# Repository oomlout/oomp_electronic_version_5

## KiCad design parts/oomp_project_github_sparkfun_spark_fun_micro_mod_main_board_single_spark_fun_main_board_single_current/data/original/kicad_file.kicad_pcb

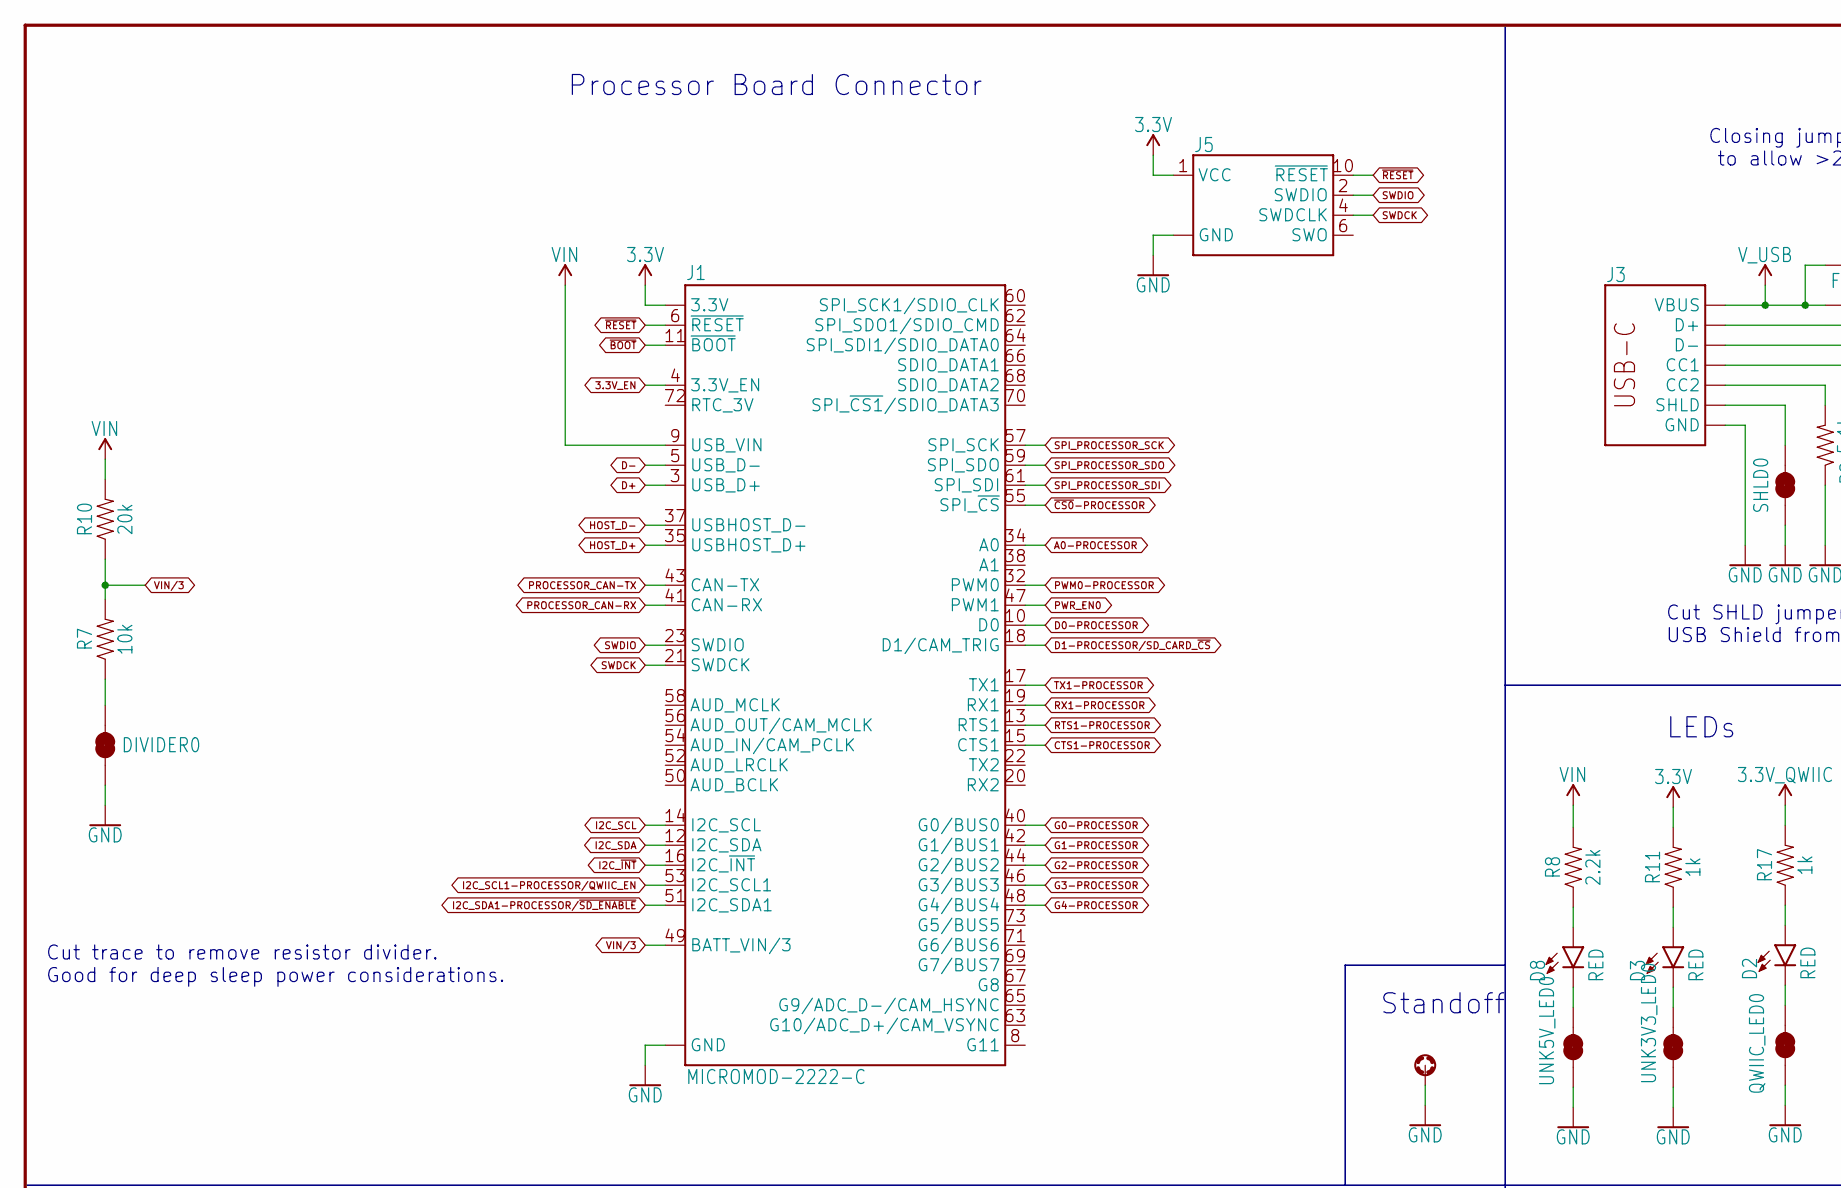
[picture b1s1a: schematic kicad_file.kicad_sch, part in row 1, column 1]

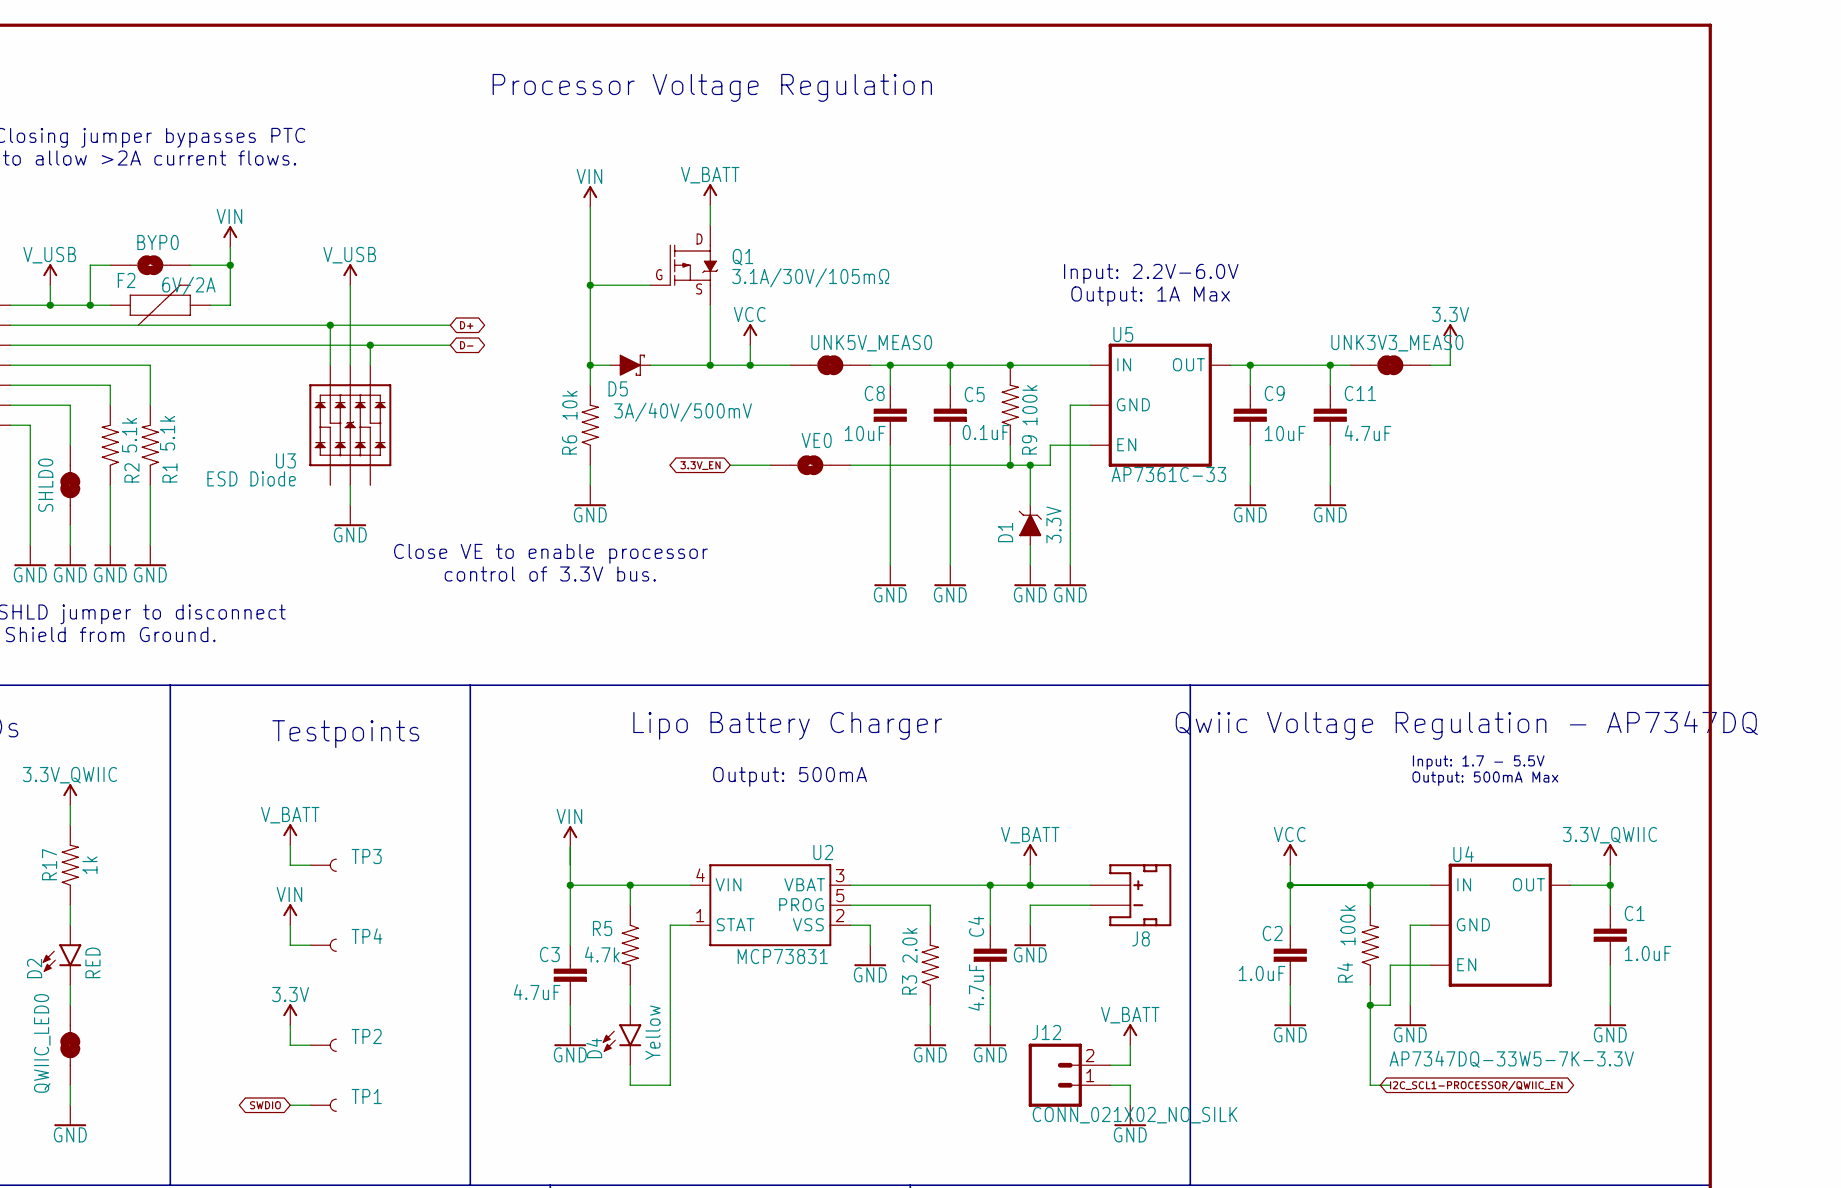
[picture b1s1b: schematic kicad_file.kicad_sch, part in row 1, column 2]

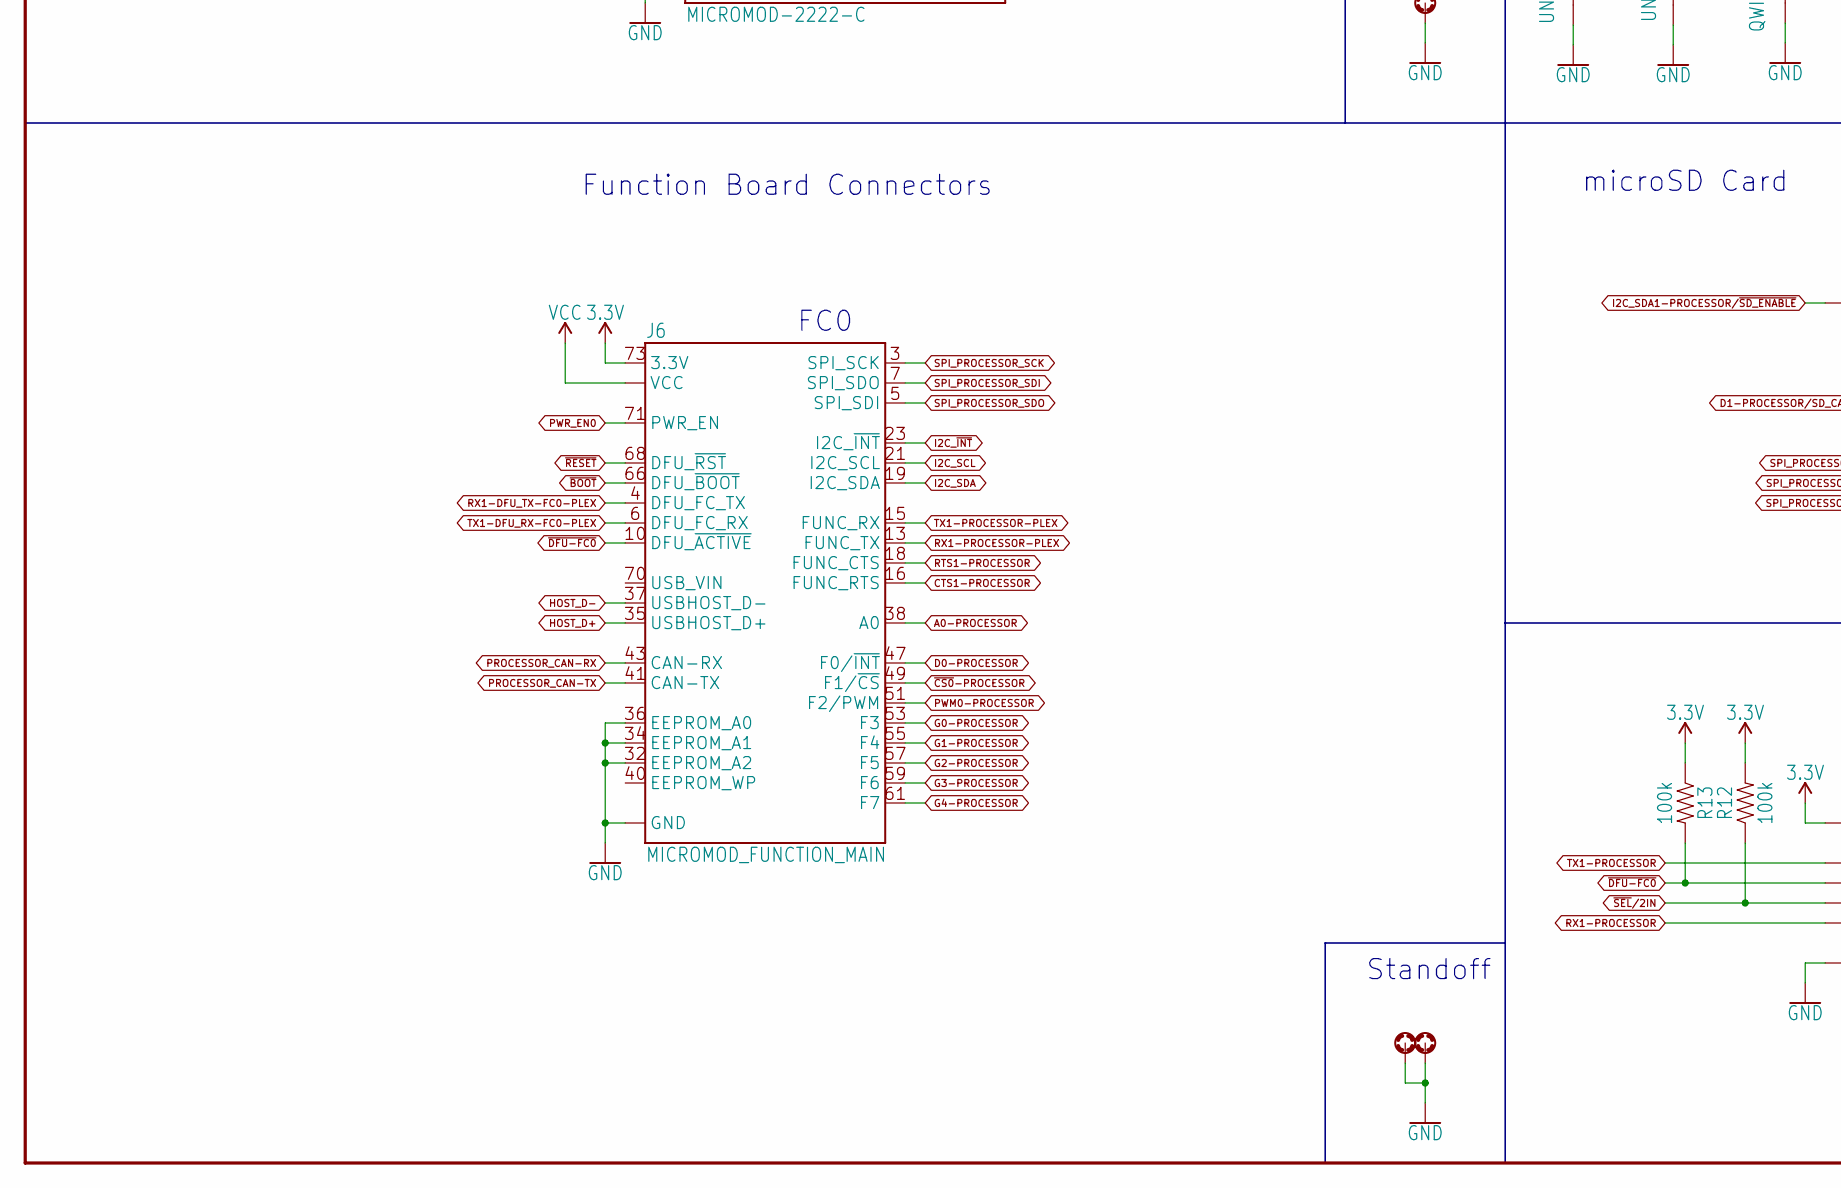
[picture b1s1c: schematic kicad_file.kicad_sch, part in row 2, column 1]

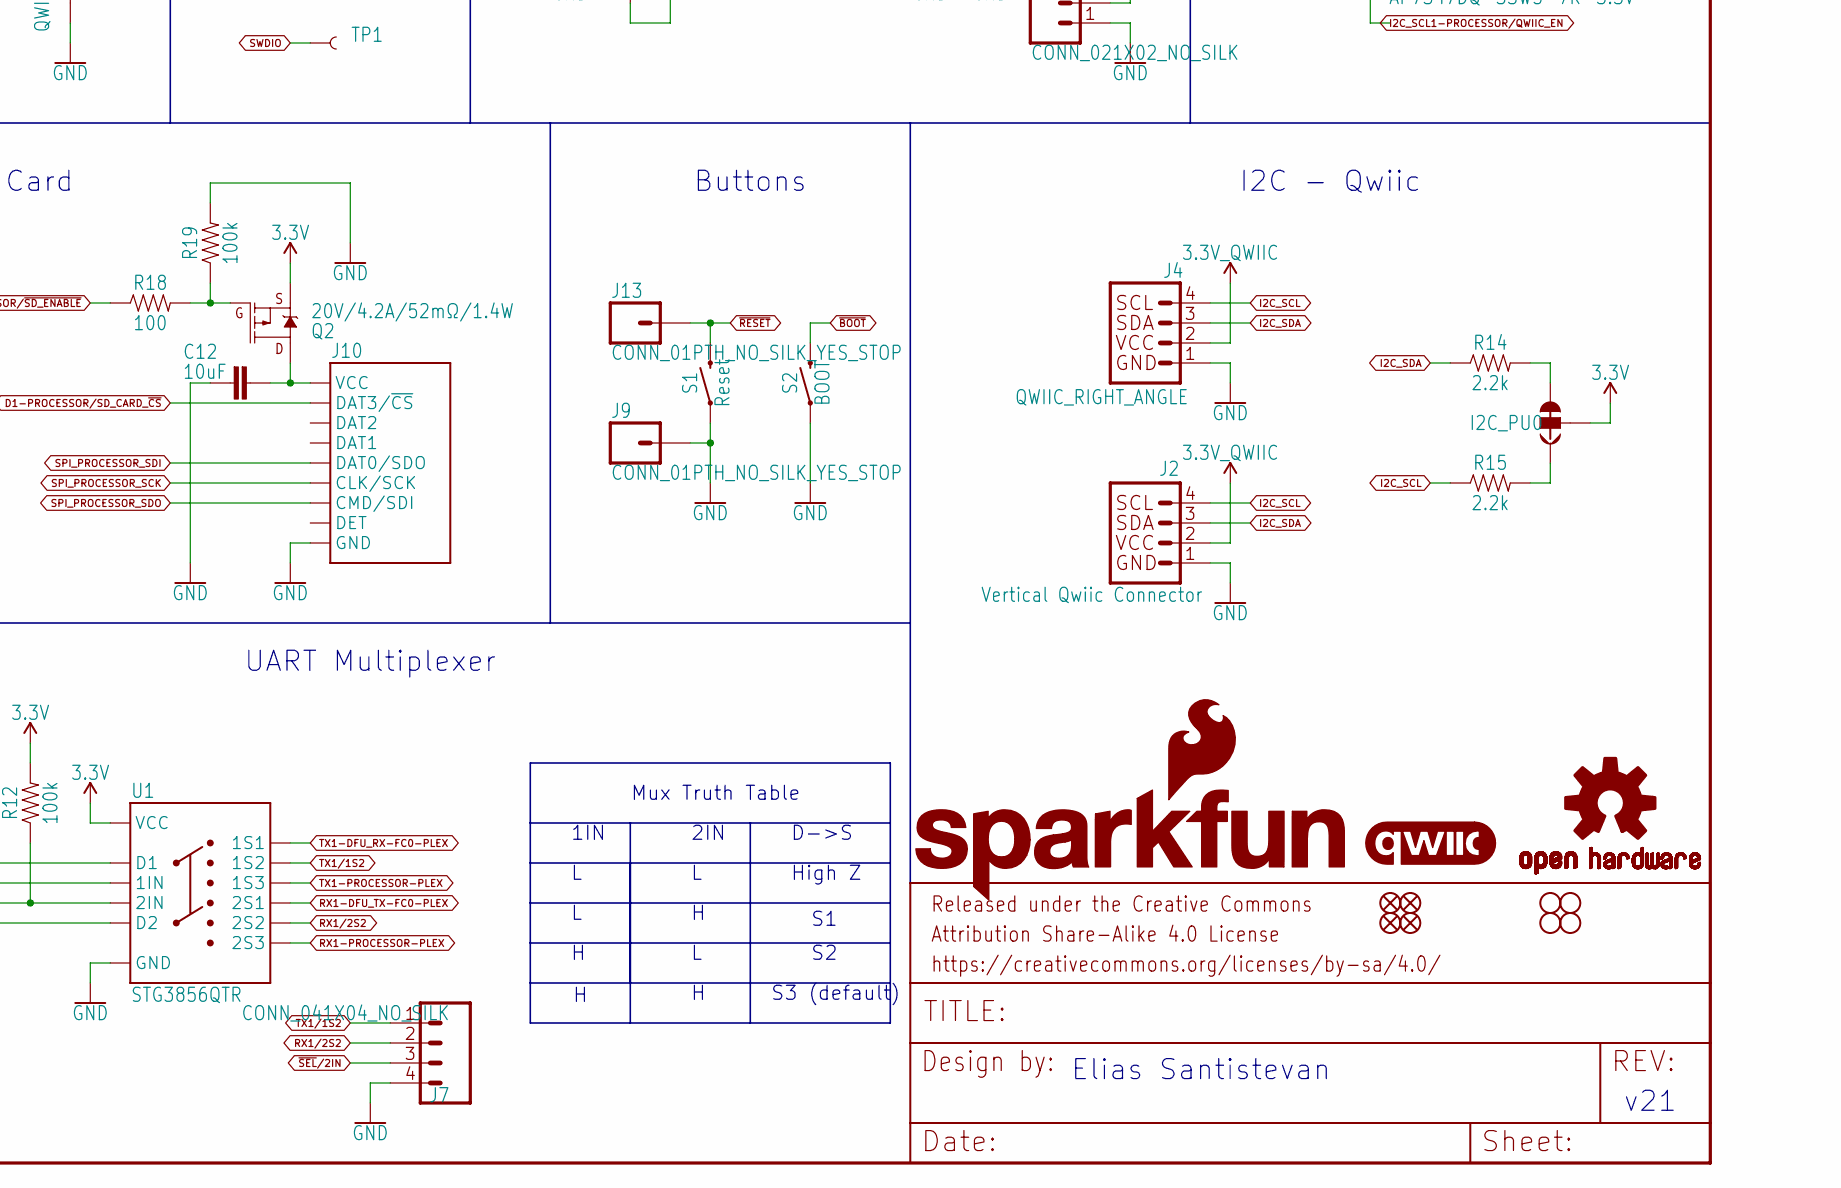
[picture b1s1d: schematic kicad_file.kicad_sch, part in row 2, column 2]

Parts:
BYP0: JUMPER-SMT_2_NO_SILK; SMT-JUMPER_2_NO_SILK
C1, C2: 1.0uF; 0603
C3, C4, C11: 4.7uF; 0603
C5: 0.1uF; 0603
C8: 10uF; 0805
C9, C12: 10uF; 0603
D1: 3.3V; SOD-323
D2, D3, D8: RED; LED-0603
D4: Yellow; LED-0603
D5: 3A/40V/500mV; SMA-DIODE
DIVIDER0: JUMPER-SMT_2_NC_TRACE_SILK; SMT-JUMPER_2_NC_TRACE_SILK
F2: 6V/2A; 1210
FD1, FD2, FD3, FD4: FIDUCIAL1X2; FIDUCIAL-1X2
FRAME1: FRAME-LEDGER; CREATIVE_COMMONS
H2, H4, H8: STAND-OFF-REFLOW-M2.5_2.5MM_TALL; STAND-OFF-REFLOW-M2.5
H14, H15, H16, H17: STAND-OFFTIGHT; STAND-OFF-TIGHT
I2C_PU0: JUMPER-SMT_3_2-NC_TRACE_SILK; SMT-JUMPER_3_2-NC_TRACE_SILK
J1: MICROMOD-2222-C; M.2-CONNECTOR-E
J2: Vertical Qwiic Connector; JST04_1MM_VERT
J3: USB_C_2-LAYER_PADS; USB-C-16P-2LAYER-PADS
J4: QWIIC_RIGHT_ANGLE; JST04_1MM_RA
J5: CORTEX_JTAG_DEBUG_MINIMUM_PTH; 2X5-PTH-1.27MM
J6: MICROMOD_FUNCTION_MAIN; M.2-CONNECTOR-E-FUNCTION-STANDARD
J7: CONN_041X04_NO_SILK; 1X04_NO_SILK
J8: JST_2MM_MALE; JST-2-SMD
J9, J13: CONN_01PTH_NO_SILK_YES_STOP; 1X01_NO_SILK
J10: MICRO-SD-PUSH-PUSH-EXT-PIN; MICROSD-EXTERNALPIN
J12: CONN_021X02_NO_SILK; 1X02_NO_SILK
LOGO1: QWIIC_LOGO_8MM; QWIIC_8MM
LOGO2: SFE_LOGO_NAME_FLAME.3_INCH; SFE_LOGO_NAME_FLAME_.3
LOGO3: OSHW-LOGOL; OSHW-LOGO-L
Q1: 3.1A/30V/105mΩ; SOT23-3
Q2: 20V/4.2A/52mΩ/1.4W; SOT23-3
QWIIC_LED0: JUMPER-SMT_2_NC_TRACE_SILK; SMT-JUMPER_2_NC_TRACE_SILK
R1, R2: 5.1k; 0603
R3: 2.0k; 0603
R4, R9, R12, R13, R19: 100k; 0603
R5: 4.7k; 0603
R6, R7: 10k; 0603
R8, R14, R15: 2.2k; 0603
R10: 20k; 0603
R11, R17: 1k; 0603
R18: 100; 0603
S1: Reset; TACTILE_SWITCH_SMD_5.2MM
S2: BOOT; TACTILE_SWITCH_SMD_5.2MM
SHLD0: JUMPER-SMT_2_NC_TRACE_SILK; SMT-JUMPER_2_NC_TRACE_SILK
TP1, TP2, TP3, TP4: TEST-POINT3X5; PAD.03X.05
U1: STG3856QTR; STG3856
U2: MCP73831; SOT23-5
U3: ESD Diode; SOT-23-6
U4: AP7347DQ-33W5-7K-3.3V; SOT25
U5: AP7361C-33; UDFN-8
UNK3V3_LED0, UNK5V_LED0: JUMPER-SMT_2_NC_TRACE_SILK; SMT-JUMPER_2_NC_TRACE_SILK
UNK3V3_MEAS0, UNK5V_MEAS0: JUMPER-COMBO_2_NC_TRACE; COMBO-JUMPER_2_NC_TRACE
VE0: JUMPER-SMT_2_NO_SILK; SMT-JUMPER_2_NO_SILK

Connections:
3.3V: I2C_PU0.2, J1.2 (3.3V), J1.74 (3.3V), J5.1 (VCC), J6.73 (3.3V), Q2.2 (S), R11.2, R12.2, R13.1, TP2.1, U1.P11 (VCC), UNK3V3_MEAS0.2, UNK3V3_MEAS0.4 (2)
3.3V_EN: J1.4 (3.3V_EN), VE0.1
3.3V_EN_VE: D1.C, R9.1, U5.5 (EN), VE0.2
3.3V_QWIIC: C1.1, J2.2, J4.2, R17.2, U4.5 (OUT)
3V3_MEAS: C9.1, C11.1, U5.1 (OUT), UNK3V3_MEAS0.1, UNK3V3_MEAS0.3 (1)
A0-PROCESSOR: J1.34 (A0), J6.38 (A0)
CTS1-PROCESSOR: J1.15 (CTS1), J6.16 (FUNC_RTS)
D0-PROCESSOR: J1.10 (D0), J6.47 (F0/~INT)
D1-PROCESSOR/SD_CARD_~CS: J1.18 (D1/CAM_TRIG), J10.2 (DAT3/~CS)
D+: J1.3 (USB_D+), J3.A6 (D+), J3.B6 (D+), U3.6 (IO4)
D-: J1.5 (USB_D-), J3.A7 (D-), J3.B7 (D-), U3.4 (IO3)
G0-PROCESSOR: J1.40 (G0/BUS0), J6.53 (F3)
G1-PROCESSOR: J1.42 (G1/BUS1), J6.55 (F4)
G2-PROCESSOR: J1.44 (G2/BUS2), J6.57 (F5)
G3-PROCESSOR: J1.46 (G3/BUS3), J6.59 (F6)
G4-PROCESSOR: J1.48 (G4/BUS4), J6.61 (F7)
GND: C1.2, C2.2, C3.2, C4.2, C5.2, C8.2, C9.2, C11.2, C12.2, D1.A, DIVIDER0.1, H2.1, H4.1, H8.1, J1.1 (GND), J1.7 (GND), J1.33 (GND), J1.36 (GND), J1.39 (GND), J1.45 (GND), J1.75 (GND), J2.1, J3.GND, J3.GND2 (GND), J4.1, J5.3 (GND), J5.5 (GND), J5.9 (GND), J6.1 (GND), J6.2 (GND), J6.8 (GND), J6.32 (EEPROM_A2), J6.33 (GND), J6.34 (EEPROM_A1), J6.36 (EEPROM_A0), J6.39 (GND), J6.45 (GND), J6.75 (GND), J7.4, J8.1 (-), J9.1, J10.6 (GND), J10.10 (GND), J10.11 (GND), J10.12 (GND), J10.13 (GND), J12.1, QWIIC_LED0.1, R1.1, R2.1, R3.1, R6.1, R19.2, S1.1, S1.2 (1), S2.1, S2.2 (1), SHLD0.1, U1.P5 (GND), U2.2 (VSS), U3.2 (VSS), U4.2 (GND), U5.4 (GND), U5.EP (GND), UNK3V3_LED0.1, UNK5V_LED0.1
HOST_D+: J1.35 (USBHOST_D+), J6.35 (USBHOST_D+)
HOST_D-: J1.37 (USBHOST_D-), J6.37 (USBHOST_D-)
I2C_SCL: J1.14 (I2C_SCL), J2.4, J4.4, J6.21 (I2C_SCL), R15.1
I2C_SCL1-PROCESSOR/QWIIC_EN: J1.53 (I2C_SCL1), R4.1, U4.3 (EN)
I2C_SDA: J1.12 (I2C_SDA), J2.3, J4.3, J6.19 (I2C_SDA), R14.1
I2C_SDA1-PROCESSOR/~SD_ENABLE: J1.51 (I2C_SDA1), R18.1
I2C_~INT: J1.16 (I2C_~INT), J6.23 (I2C_~INT)
unnamed: D8.C, UNK5V_LED0.2
unnamed: D3.A, R11.1
unnamed: J3.B5 (CC2), R2.2
unnamed: J3.A5 (CC1), R1.2
unnamed: R3.2, U2.5 (PROG)
unnamed: DIVIDER0.2, R7.1
unnamed: D4.C, U2.1 (STAT)
unnamed: D4.A, R5.2
unnamed: D3.C, UNK3V3_LED0.2
unnamed: I2C_PU0.3, R14.2
unnamed: D8.A, R8.1
unnamed: I2C_PU0.1, R15.2
unnamed: D2.A, R17.1
unnamed: D2.C, QWIIC_LED0.2
unnamed: C12.1, J10.4 (VCC), Q2.3 (D)
unnamed: Q2.1 (G), R18.2, R19.1
PROCESSOR_CAN-RX: J1.41 (CAN-RX), J6.43 (CAN-RX)
PROCESSOR_CAN-TX: J1.43 (CAN-TX), J6.41 (CAN-TX)
PWM0-PROCESSOR: J1.32 (PWM0), J6.51 (F2/PWM)
PWR_EN0: J1.47 (PWM1), J6.71 (PWR_EN)
RTS1-PROCESSOR: J1.13 (RTS1), J6.18 (FUNC_CTS)
RX1-DFU_TX-FC0-PLEX: J6.4 (DFU_FC_TX), U1.P9 (2S1)
RX1-PROCESSOR: J1.19 (RX1), U1.P6 (D2)
RX1-PROCESSOR-PLEX: J6.13 (FUNC_TX), U1.P7 (2S3)
RX1/2S2: J7.2, U1.P8 (2S2)
SHLD: J3.SHLD1 (SHLD), J3.SHLD2 (SHLD), J3.SHLD3 (SHLD), J3.SHLD4 (SHLD), SHLD0.2
SPI_PROCESSOR_SCK: J1.57 (SPI_SCK), J6.3 (SPI_SCK), J10.5 (CLK/SCK)
SPI_PROCESSOR_SDI: J1.61 (SPI_SDI), J6.7 (SPI_SDO), J10.7 (DAT0/SDO)
SPI_PROCESSOR_SDO: J1.59 (SPI_SDO), J6.5 (SPI_SDI), J10.3 (CMD/SDI)
SWDCK: J1.21 (SWDCK), J5.4 (SWDCLK)
SWDIO: J1.23 (SWDIO), J5.2 (SWDIO), TP1.1
TX1-DFU_RX-FC0-PLEX: J6.6 (DFU_FC_RX), U1.P1 (1S1)
TX1-PROCESSOR: J1.17 (TX1), U1.P4 (D1)
TX1-PROCESSOR-PLEX: J6.15 (FUNC_RX), U1.P3 (1S3)
TX1/1S2: J7.1, U1.P2 (1S2)
VCC: C2.1, D5.C, J6.72 (VCC), J6.74 (VCC), Q1.2 (S), R4.2, U4.1 (IN), UNK5V_MEAS0.1, UNK5V_MEAS0.3 (1)
VCC_MEAS: C5.1, C8.1, R9.2, U5.8 (IN), UNK5V_MEAS0.2, UNK5V_MEAS0.4 (2)
VIN: BYP0.2, C3.1, D5.A, F2.2, J1.9 (USB_VIN), Q1.1 (G), R5.1, R6.2, R8.2, R10.2, TP4.1, U2.4 (VIN)
VIN/3: J1.49 (BATT_VIN/3), R7.2, R10.1
V_BATT: C4.1, J8.2 (+), J12.2, Q1.3 (D), TP3.1, U2.3 (VBAT)
V_USB: BYP0.1, F2.1, J3.VBUS1 (VBUS), J3.VBUS2 (VBUS), U3.5 (VCC)
~BOOT: J1.11 (~BOOT), J6.66 (DFU_~BOOT), S2.3 (2), S2.4 (2)
~CS0-PROCESSOR: J1.55 (SPI_~CS), J6.49 (F1/~CS)
~DFU-FC0: J6.10 (DFU_~ACTIVE), R13.2, U1.P12 (1IN)
~RESET: J1.6 (~RESET), J5.10 (~RESET), J6.68 (DFU_~RST), J13.1, S1.3 (2), S1.4 (2)
~SEL/2IN: J7.3, R12.1, U1.P10 (2IN)

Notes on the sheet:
Elias Santistevan
Buttons
Close VE to enable processor control of 3.3V bus.
Function Board Connectors
FC0
Lipo Battery Charger
Mux Truth Table
Standoff
2IN
Processor Board Connector
Input: 2.2V-6.0V Output: 1A Max
S3 (default)
I2C - Qwiic
Testpoints
UART Multiplexer
microSD Card
D->S
Output: 500mA
Closing jumper bypasses PTC to allow >2A current flows.
Cut trace to remove resistor divider. Good for deep sleep power considerations.
LEDs
Processor Voltage Regulation
v21
Input: 1.7 - 5.5V Output: 500mA Max
Qwiic Voltage Regulation - AP7347DQ
1IN
High Z
Cut SHLD jumper to disconnect USB Shield from Ground.

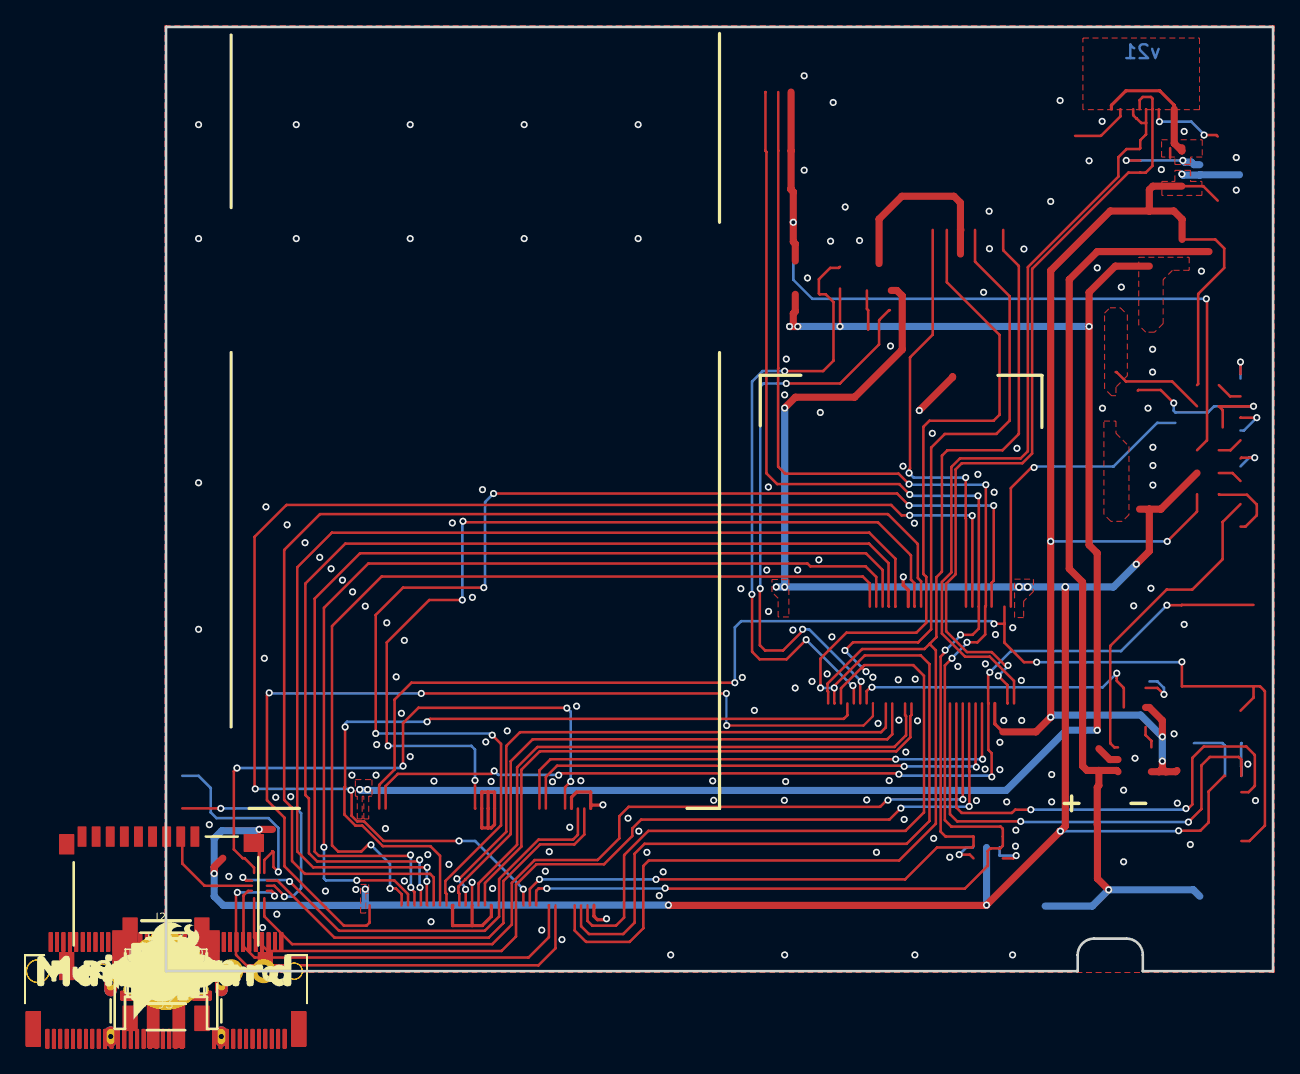
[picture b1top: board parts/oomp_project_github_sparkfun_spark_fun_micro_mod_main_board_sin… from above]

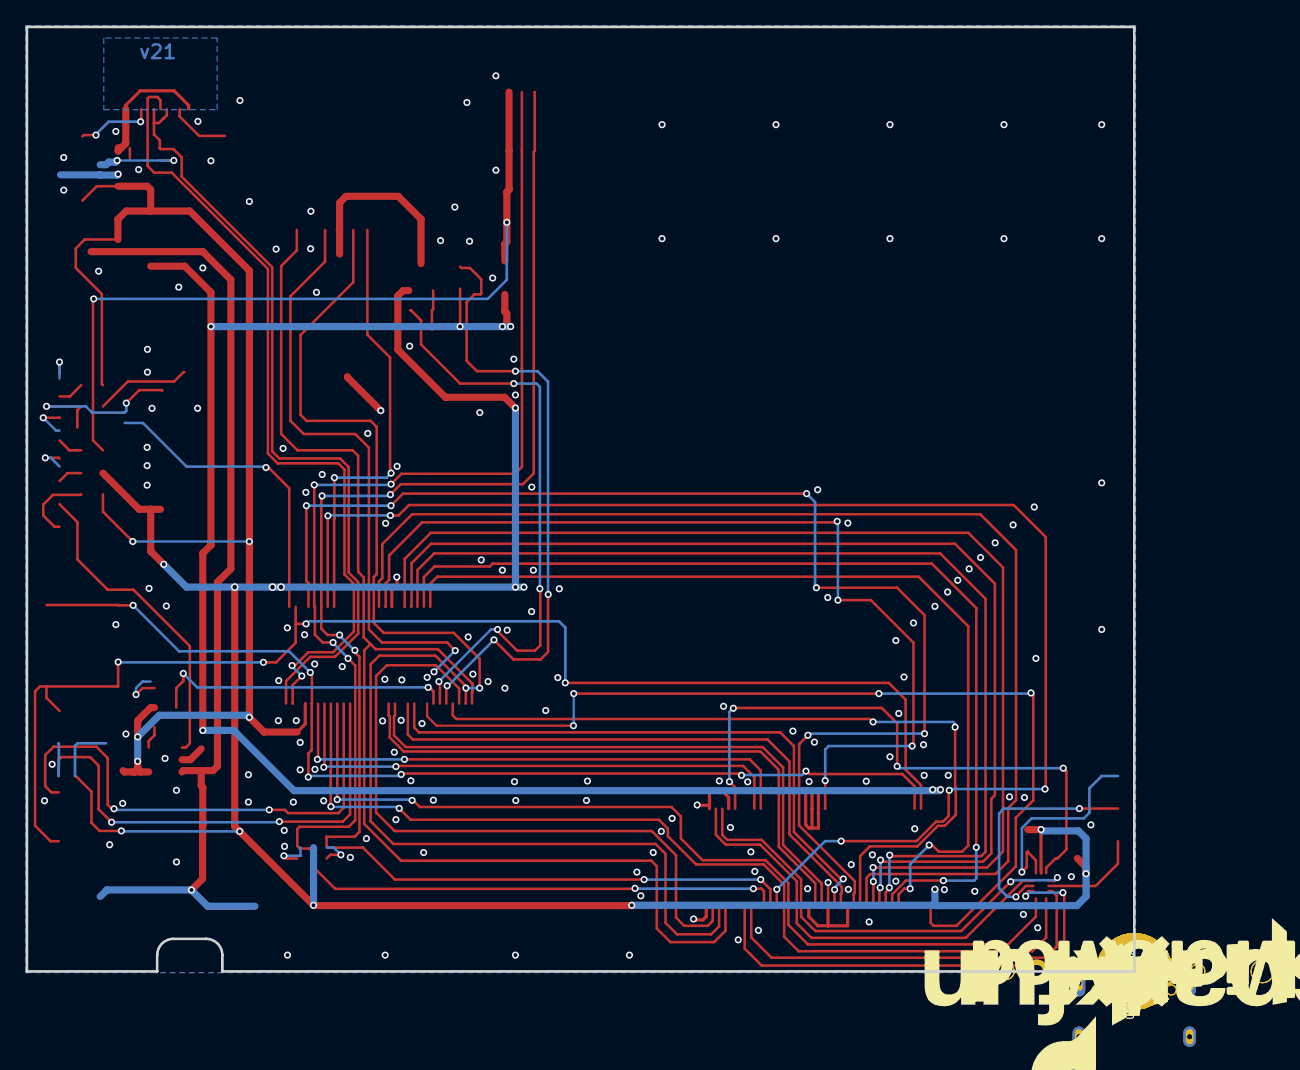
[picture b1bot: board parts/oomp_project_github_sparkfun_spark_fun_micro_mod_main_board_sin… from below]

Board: 2 copper layers, 86.4 x 73.7 mm, 130 parts (32 on the bottom side), 70 nets.

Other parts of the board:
FRAME2: FRAME-LEDGERNO_FOOTPRINT; DUMMY
H1: STAND-OFFTIGHT; STAND-OFF-TIGHT
U$1: #TXO#7
U$2: #RXI#6
U$3: #PTC#15
U$4: 3V332533
U$5: VIN32532
U$6: CHG32531
U$7: #SHLD#501
U$8: BOOT32541
U$9: RESET32540
U$10: PROCESSOR525
U$11: FUNCTION_ZERO520
U$12: ##SEL##5
U$13: MAIN523
U$14: MICROMOD_MI_LOGO_1
U$15: 0523
U$16, U$29: #GND#3
U$17: MICROMOD_LOGO_1
U$18: BOARD524
U$19: ##SEL##3
U$20: #RXI#4
U$21: MAIN_BOARD5523
U$22: QWIIC_3MM
U$23: STANDOFF501
U$24: SFE_LOGO_FLAME_.3
U$25, U$32: SWD6522
U$26: #3V3_MEAS#6522
U$27: CHARGE501
U$28: #TXO#5
U$30: #I2C#501
U$31: #5V_MEAS#6522
U$33: 500MA6520
U$34: SFE_LOGO_NAME_FLAME_.1
U$35: QWC4
U$36, U$37: #GND#10
U$38: ##RST##8
U$39: #VBAT#9
U$49: #3V3_EN#23
U$50: #3V3_LED#22
U$51: #QWIIC_LED#22
U$52: #DIVIDER#23
U$53: #VIN_LED#24

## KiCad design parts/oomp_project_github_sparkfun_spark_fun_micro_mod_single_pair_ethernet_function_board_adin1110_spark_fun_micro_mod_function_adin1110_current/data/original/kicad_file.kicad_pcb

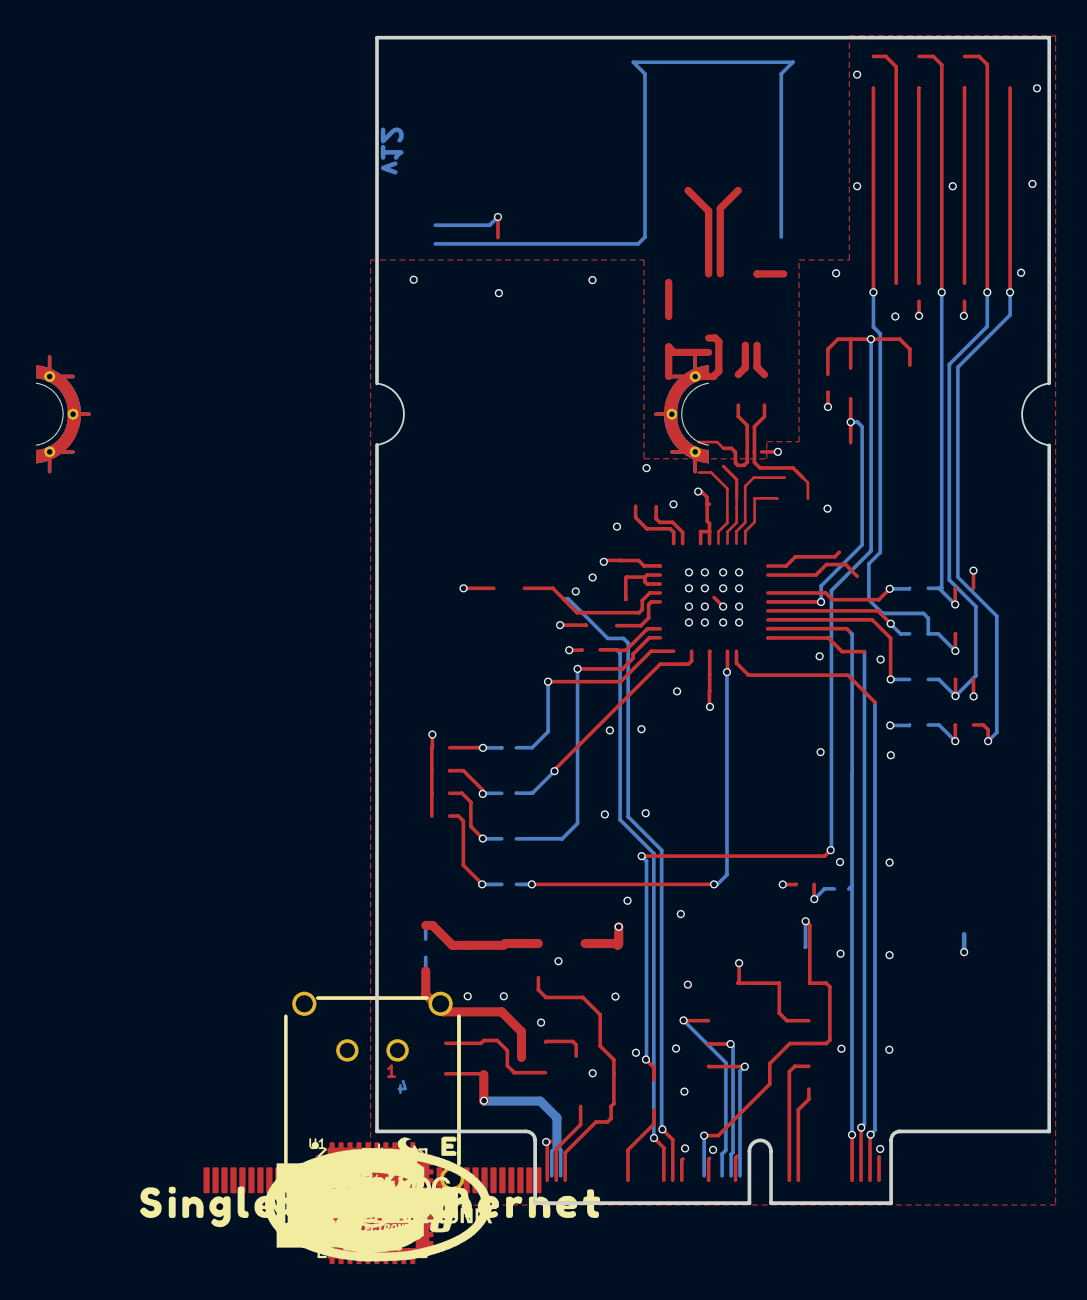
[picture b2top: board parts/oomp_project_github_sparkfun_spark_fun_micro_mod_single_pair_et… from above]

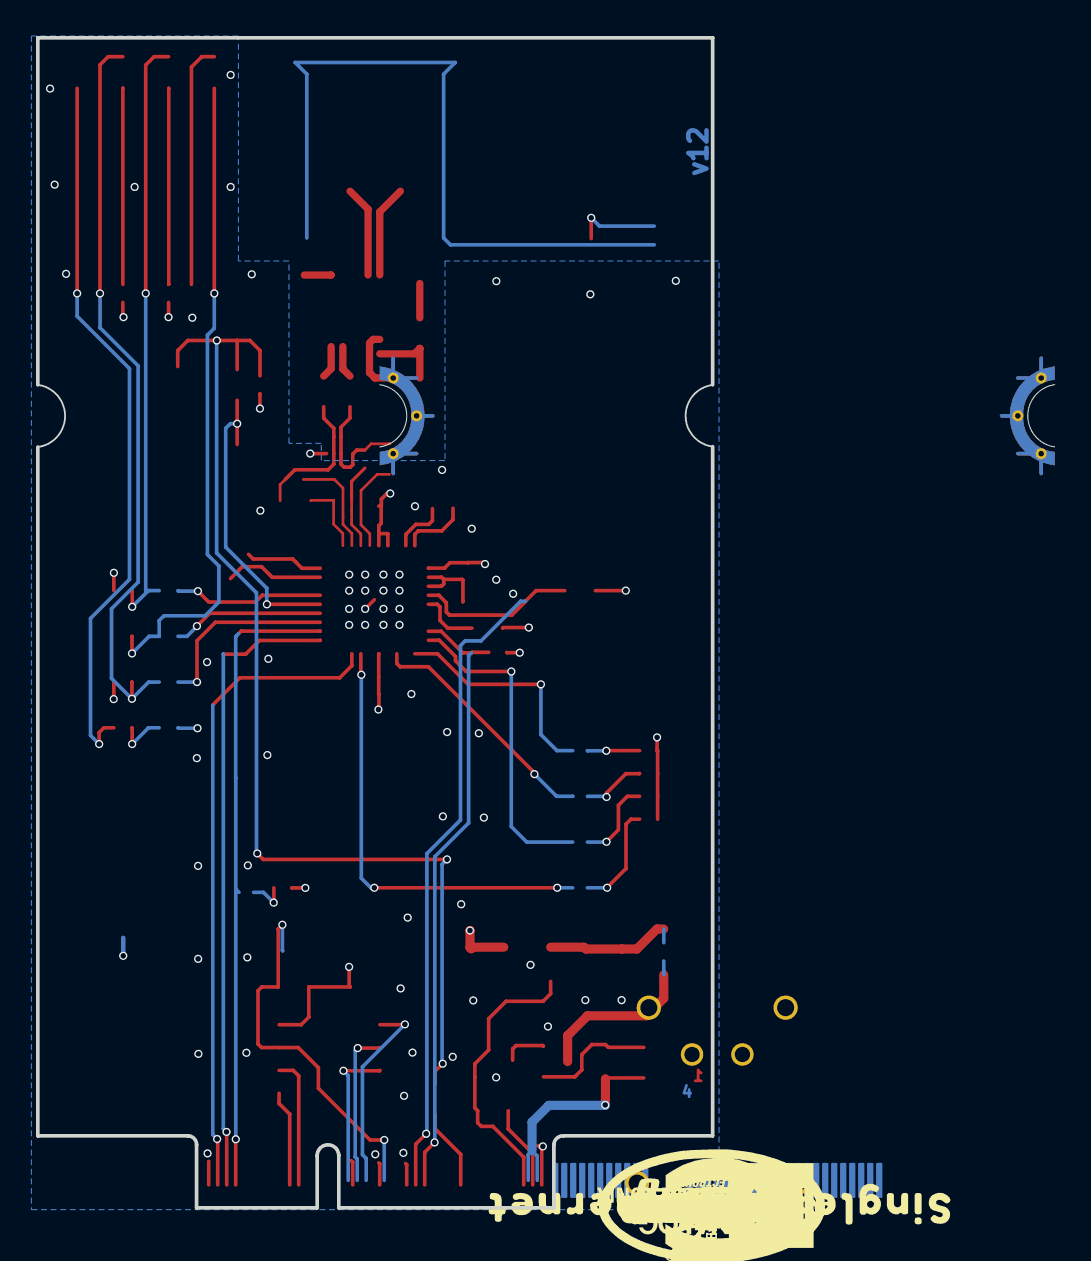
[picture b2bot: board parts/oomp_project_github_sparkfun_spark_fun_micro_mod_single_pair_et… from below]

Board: 4 copper layers, 37.5 x 65.0 mm, 129 parts (38 on the bottom side), 65 nets.

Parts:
C1, C2: 0.22uF; 0603
C3, C4: 0.1uF; 0603
C5, C6: 10pF; 0603
C7: 3.3nF; 0603
C8, C9: 1.0uF; 0603
C10, C13, C15, C16, C18, C23: 0.1uF; 0402-TIGHT
C11: 0.68uF; 0603
C12, C14, C17: 10nF; 0402-TIGHT
C19: 1.0uF; 0402-TIGHT
C20: 1.0nF/2kV; 1206
C21: 0.1uF/50V; 0603
C22: 470nF/100V; 0805
CIPO0: TEST-POINTTP_15TH_THRU; TP_15TH
COPI0: TEST-POINTTP_15TH_THRU; TP_15TH
CS0: TEST-POINTTP_15TH_THRU; TP_15TH
EWP0: JUMPER-SMT_2_NO_SILK; SMT-JUMPER_2_NO_SILK
FD1, FD2, FD3, FD4: FIDUCIALUFIDUCIAL; FIDUCIAL-MICRO
FRAME1: FRAME-LEDGER; CREATIVE_COMMONS
INT0: TEST-POINTTP_15TH_THRU; TP_15TH
J1: IP20(RJ50); T1_INDUSTRIAL_JACK_AH_IP20
J2: MICROMOD_FUNCTION_STANDARD; M.2-CARD-E-22_FUNCTION_STANDARD
LED-0, LED-1: JUMPER-SMT_2_NC_TRACE_SILK; SMT-JUMPER_2_NC_TRACE_SILK
LED-LINK0: JUMPER-SMT_2_NC_TRACE_SILK; SMT-JUMPER_2_NC_TRACE_SILK
LED-PWR0: JUMPER-SMT_2_NC_TRACE_SILK; SMT-JUMPER_2_NC_TRACE_SILK
LED_0: Green; LED-0603
LED_1: Yellow; LED-0603
LINK_ST0: Blue; LED-0603
LOGO1: SFE_LOGO_NAME_FLAME.1_INCH; SFE_LOGO_NAME_FLAME_.1
LOGO2: SPECIAL_INSTRUCTIONS-ORDERING; ORDERING_INSTRUCTIONS
LOGO3: OSHW-LOGOMINI; OSHW-LOGO-MINI
MEAS0: JUMPER-COMBO_2_NC_TRACE; COMBO-JUMPER_2_NC_TRACE
MS_SEL0: SMT-JUMPER_2_NO_SILK
PWR0: Red; LED-0603
Q1: 220mA/50V/3.5Ω; SOT23-3
Q2: 20V/4.2A/52mΩ/1.4W; SOT23-3
R1, R2: 49.9; 0603
R3, R4: 5.1k; 0402-TIGHT
R5, R6: 10.2k; 0402-TIGHT
R7, R8, R22: 10k; 0603
R9, R11, R20, R21: 1k; 0402-TIGHT
R10, R24: 1.5k; 0603
R12, R13, R14, R15, R16, R17, R18, R19, R25: 4.7k; 0402-TIGHT
R23, R29: 100Ω; 0603
R26: 100; 0603
R27: 4.7k; 0603
R28: 100k; 0402-TIGHT
S1: RESET; TACTILE_SWITCH_SMD_5.2MM
SHLD0: SMT-JUMPER_3_1-NC_TRACE_SILK
SPI0: TEST-POINTTP_15TH_THRU; TP_15TH
SPI_CFG0, SPI_CFG1: SMT-JUMPER_2_NO_SILK
SWPD0: SMT-JUMPER_2_NO_SILK
T1: WE-STST; WE_STST_TRANSFORMER_1_1_SMD_3.2X4.7MM_74930030
TP1: TEST-POINT3X4; PAD.03X.04
TX2P4: SMT-JUMPER_2_NO_SILK
U1: ADIN1110; LFCSP-40
U2: EEPROM; SO08
U3: 3.3V; SOT23-5
U4: WE-TVS; WE_TVS_1.0X1.2MM
U$1: #RESET#0
U$2: HARTING_LOGO; HARTING_LOGO_9MM
U$4, U$21: ADIN11100
U$5: DIGIKEY_LOGO
U$6: #PWR#19
U$7: PWR0
U$8: SHLD11
U$9: #EWP#18
U$10: #LED0#20
U$11: #GND#16
U$12: #CAP#17
U$13: ##TX2P4_EN##4
U$14: #SPI_CFG1#0
U$15: #MS_SEL#2
U$16: #SPI_CFG0#0
U$17, U$18: SINGLE_PAIR_ETHERNET0
U$19: WURTH_LOGO; WURTH_LOGO_9MM
U$20: ANALOG_DEVICE_LOGO_9MM
U$22: ##SWPD_EN##4
U$23: LED_03
U$24, U$26: FUNCTION0
U$25: LED_14
U$27: LINK_ST15
U$28: #MEAS#3
U$29: #LED1#21
U$30: HARTING_LOGO_9MM
U$31: #LINKST#2
U$32: WURTH_LOGO_9MM
U$33: ANALOG_DEVICES_LOGO; ANALOG_DEVICE_LOGO_9MM
U$34: DIGIKEY_LOGO
U$35: SFE_LOGO_NAME_FLAME_.1
U$37, U$63: MICROMOD_LOGO_.35
Y1: 25MHz; CRYSTAL-SMD-2.0X1.6MM-WE

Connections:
1.1V: C11.1, C15.1, U1.23, U1.24
3.3V: C4.1, C9.1, C10.1, C12.1, C13.1, C14.1, C16.1, C17.1, LED-PWR0.2, R8.1, R10.2, R11.1, R12.2, R13.2, R14.2, R15.2, R16.2, R17.2, R18.2, R20.1, R24.2, R25.2, R28.2, TP1.1, U1.16, U1.17, U1.22, U1.35, U2.8, U3.5
3.3V_IN: J2.73, R22.1
A0: J2.36, U2.1
A1: J2.34, U2.2
A2: J2.32, U2.3
DA+: J1.1, T1.7
DA-: J1.2, T1.6
EWP: EWP0.2, J2.40, R8.2, U2.7
GND: C3.2, C4.2, C5.2, C6.2, C7.2, C8.2, C9.2, C10.2, C11.2, C12.2, C13.2, C14.2, C15.2, C16.2, C17.2, C18.2, C19.2, C20.2, C21.2, C23.2, EWP0.1, J2.1, J2.2, J2.8, J2.33, J2.39, J2.45, J2.75, J2.GND1, J2.GND2, J2.GND3, J2.GND4, J2.GND5, J2.GND6, PWR0.C, Q1.2, R19.2, R21.1, S1.1, SHLD0.1, U1.EP, U2.4, U3.2, U4.3, Y1.2, Y1.4
I2C_SCL: J2.21, U2.6
I2C_SDA: J2.19, U2.5
LED_0: LED-0.2, U1.3
LED_1: LED-1.2, U1.6
LINK_ST: LED-LINK0.2, U1.4
MS_SEL: MS_SEL0.1, U1.30
unnamed: MEAS0.1, MEAS0.3, Q2.3
unnamed: C3.1, C8.1, MEAS0.2, MEAS0.4, U3.1
unnamed: C21.1, T1.5
unnamed: C22.1, T1.4
unnamed: LED-LINK0.1, LINK_ST0.A, R19.1
unnamed: LED-1.1, LED_1.C, R18.1
unnamed: C22.2, R23.1, T1.3
unnamed: C20.1, R23.2
unnamed: LED-0.1, LED_0.C, R17.1
unnamed: Q1.3, R26.1
unnamed: Q2.1, R7.1, R26.2
unnamed: C5.1, U1.8, Y1.1
unnamed: C23.1, R27.1, U1.5
unnamed: C6.1, U1.9, Y1.3
unnamed: R27.2, R28.1, R29.2, S1.3
unnamed: R10.1, U1.26
unnamed: LED-PWR0.1, R9.2
unnamed: PWR0.A, R9.1
unnamed: C18.1, U1.19
unnamed: C19.1, U1.20
unnamed: LED_0.A, R11.2
unnamed: C1.1, R2.1, R4.1, U4.2, U4.5
unnamed: MS_SEL0.2, R14.1
unnamed: R13.1, SWPD0.2
unnamed: R12.1, TX2P4.2
unnamed: R16.1, SPI_CFG0.2
unnamed: R15.1, SPI_CFG1.2
unnamed: LED_1.A, R20.2
unnamed: C2.1, R1.1, R3.2, U4.1, U4.6
unnamed: C1.2, T1.1
unnamed: LINK_ST0.C, R21.2
unnamed: C2.2, T1.2
unnamed: R4.2, R6.2, U1.13
unnamed: R3.1, R5.1, U1.14
unnamed: R1.2, R6.1, U1.15
unnamed: R2.2, R5.2, U1.12
unnamed: C7.1, SHLD0.3
unnamed: J1.S1, J1.S2, J1.S3, J1.S4, SHLD0.2
PWR_EN: J2.71, Q1.1, R22.2, U3.3
SPI_CFG1: SPI_CFG1.1, U1.37
SPI_PICO: COPI0.1, J2.5, U1.1
SPI_POCI/SPI_CFG0: CIPO0.1, J2.7, SPI_CFG0.1, U1.2
SPI_SCK: J2.3, SPI0.1, U1.38
VCC_IN: J2.72, J2.74, Q2.2, R7.2
~CS: CS0.1, J2.49, R25.1, U1.29
~INT: INT0.1, J2.47, R24.1, U1.25
~RESET: J2.57, R29.1
~SWPD_EN: SWPD0.1, U1.33
~TX2P4_EN: TX2P4.1, U1.31

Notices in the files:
parts/oomp_project_github_sparkfun_spark_fun_micro_mod_main_board_single_spark_fun_main_board_single_current/data/original/kicad_file.kicad_sch:
Released under the Creative Commons
https://creativecommons.org/licenses/by-sa/4.0
parts and their libraries:
Released under the Creative Commons Attribution Share-Alike 4.0 License
